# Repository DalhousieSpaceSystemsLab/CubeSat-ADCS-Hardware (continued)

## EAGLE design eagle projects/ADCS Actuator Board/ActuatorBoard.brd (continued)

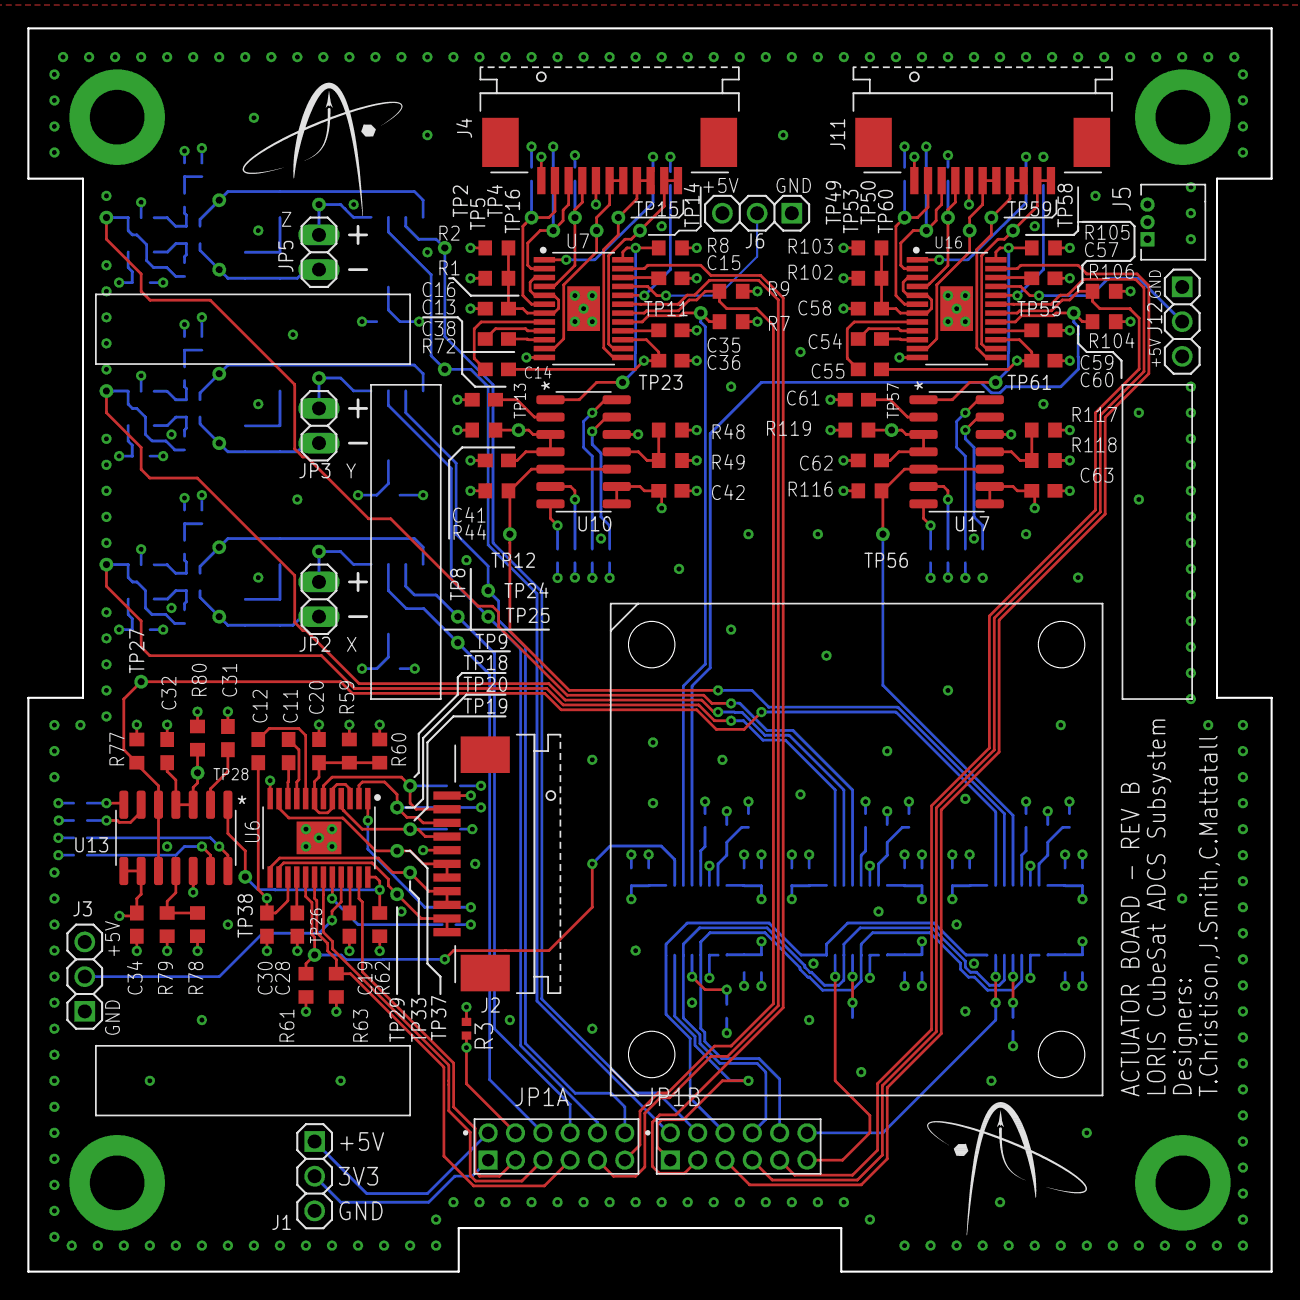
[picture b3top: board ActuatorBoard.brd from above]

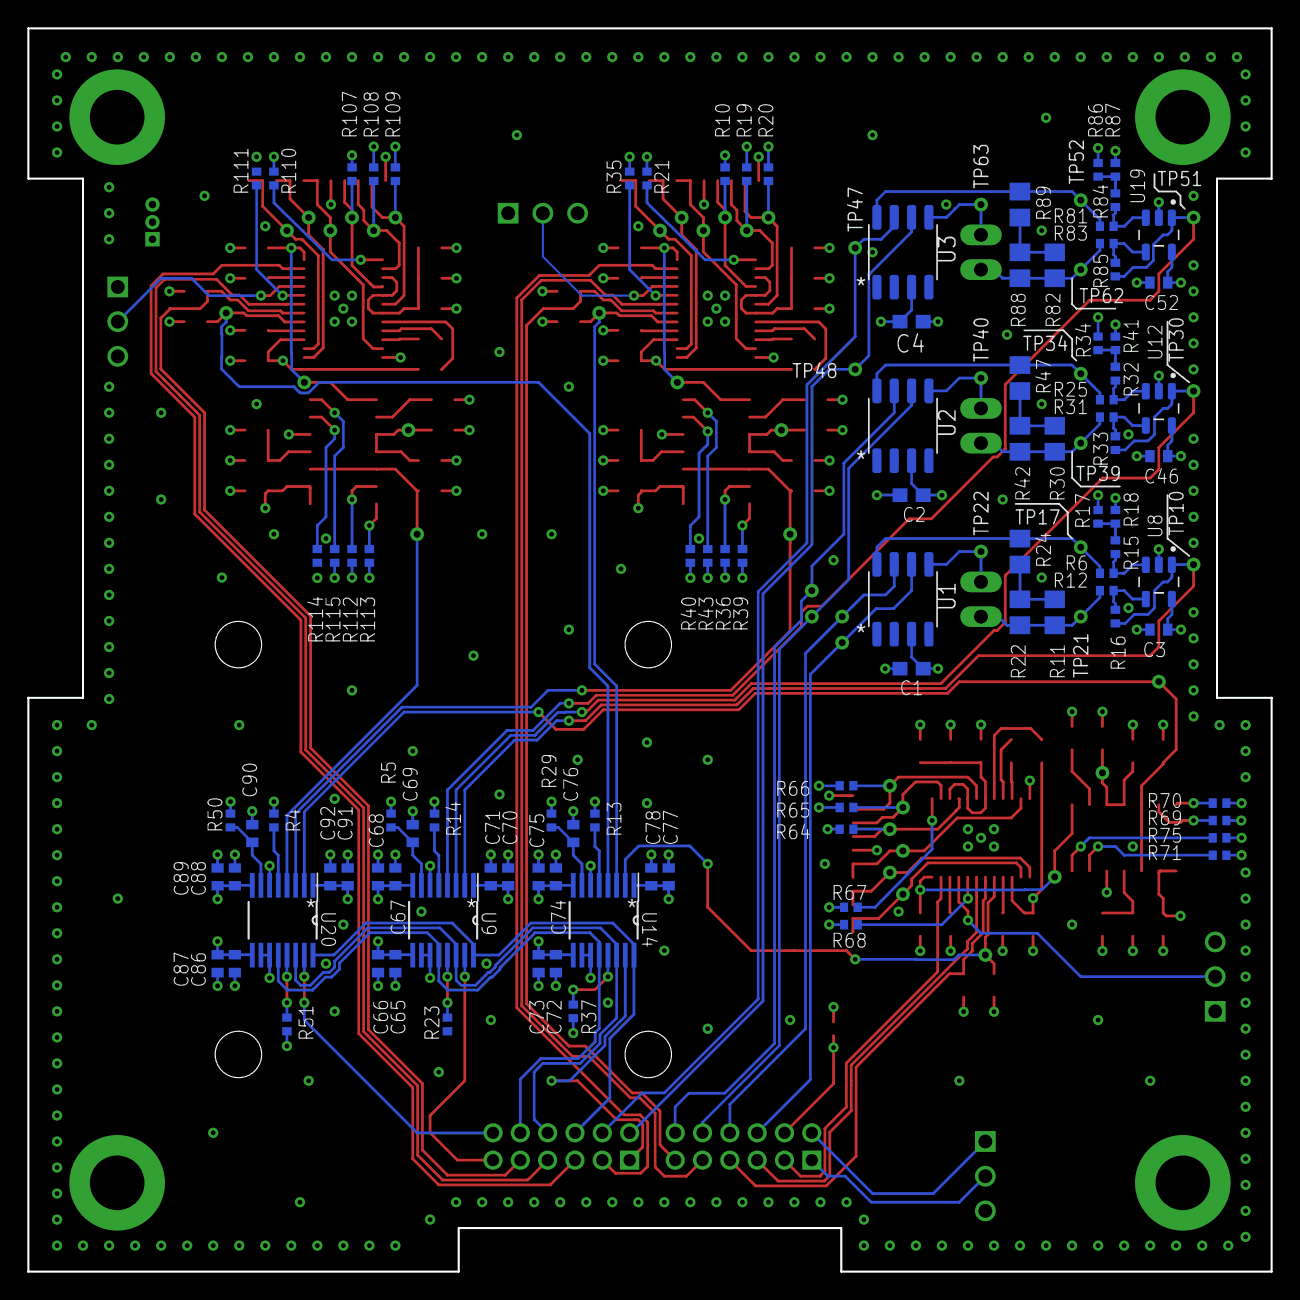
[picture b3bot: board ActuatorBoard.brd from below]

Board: 4 copper layers, 91.0 x 91.0 mm, 228 parts (117 on the bottom side), 133 nets.

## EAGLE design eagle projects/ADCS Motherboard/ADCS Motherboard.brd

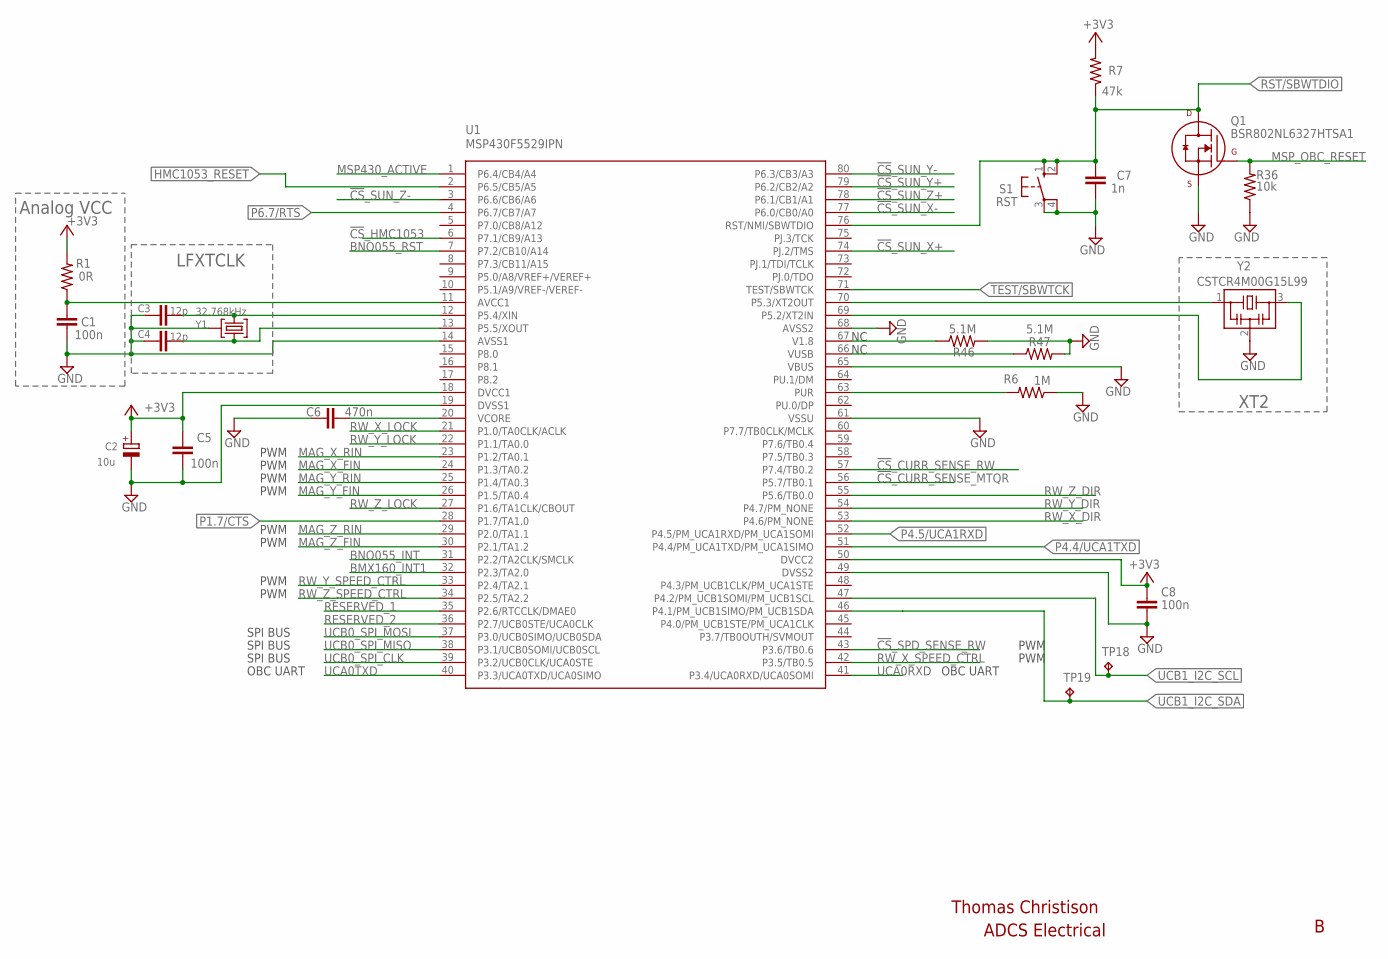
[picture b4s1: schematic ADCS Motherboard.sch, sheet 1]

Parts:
C1, C5, C8: 100n; C0402
C2: 10u; A/3216-18R
C3, C4: 12p; C0402
C6: 470n; C0402
C7: 1n; C0402
Q1: BSR802NL6327HTSA1; SOT23-3P95_230X110L20X43N_PMV16XN
R1: 0R; R0402
R6: 1M; R0603
R7: 47k; R0402
R36: 10k; R0603
R46, R47: 5.1M; R0402
S1: RST; B3F-10XX
TP18, TP19: TESTPOINT; TP_P76H50
U1: MSP430F5529IPN; QFP80P50_1400X1400X160L60X22N
Y1: 32.768kHz; MS3V-T1R
Y2: CSTCR4M00G15L99; MURATA-FILTER_CSTCR

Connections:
!CS!_CURR_SENSE_MTQR: U1.56 (P5.7/TB0.1); also elsewhere on the board
!CS!_CURR_SENSE_RW: U1.57 (P7.4/TB0.2); also elsewhere on the board
!CS!_HMC1053: U1.6 (P7.1/CB9/A13); also elsewhere on the board
!CS!_SPD_SENSE_RW: U1.43 (P3.6/TB0.6); also elsewhere on the board
!CS!_SUN_X+: U1.74 (PJ.2/TMS); also elsewhere on the board
!CS!_SUN_X-: U1.77 (P6.0/CB0/A0); also elsewhere on the board
!CS!_SUN_Y+: U1.79 (P6.2/CB2/A2); also elsewhere on the board
!CS!_SUN_Y-: U1.80 (P6.3/CB3/A3); also elsewhere on the board
!CS!_SUN_Z+: U1.78 (P6.1/CB1/A1); also elsewhere on the board
!CS!_SUN_Z-: U1.3 (P6.6/CB6/A6); also elsewhere on the board
+3V3: C2.+, C5.2, C8.1, R1.2, R7.2, U1.18 (DVCC1), U1.50 (DVCC2); also elsewhere on the board
AVCC1: C1.1, R1.1, U1.11 (AVCC1)
BMX160_INT1: U1.32 (P2.3/TA2.0); also elsewhere on the board
BNO055_INT: U1.31 (P2.2/TA2CLK/SMCLK); also elsewhere on the board
BNO055_RST: U1.7 (P7.2/CB10/A14); also elsewhere on the board
GND: C1.2, C2.-, C3.1, C4.1, C5.1, C6.1, C7.2, C8.2, Q1.2 (S), R6.1, R36.1, R46.2, R47.2, S1.3, S1.4 (P1), U1.14 (AVSS1), U1.19 (DVSS1), U1.49 (DVSS2), U1.61 (VSSU), U1.65 (VBUS), U1.68 (AVSS2), Y1.P3 (GND), Y2.2; also elsewhere on the board
HMC1053_RESET: U1.2 (P6.5/CB5/A5); also elsewhere on the board
MAG_X_FIN: U1.24 (P1.3/TA0.2); also elsewhere on the board
MAG_X_RIN: U1.23 (P1.2/TA0.1); also elsewhere on the board
MAG_Y_FIN: U1.26 (P1.5/TA0.4); also elsewhere on the board
MAG_Y_RIN: U1.25 (P1.4/TA0.3); also elsewhere on the board
MAG_Z_FIN: U1.30 (P2.1/TA1.2); also elsewhere on the board
MAG_Z_RIN: U1.29 (P2.0/TA1.1); also elsewhere on the board
MSP430_ACTIVE: U1.1 (P6.4/CB4/A4)
MSP_OBC_RESET: Q1.1 (G), R36.2; also elsewhere on the board
unnamed: R46.1, U1.67 (V1.8)
unnamed: R47.1, U1.66 (VUSB)
P1.7/CTS: U1.28 (P1.7/TA1.0); also elsewhere on the board
P4.4/UCA1TXD: U1.51 (P4.4/PM_UCA1TXD/PM_UCA1SIMO); also elsewhere on the board
P4.5/UCA1RXD: U1.52 (P4.5/PM_UCA1RXD/PM_UCA1SOMI); also elsewhere on the board
P5.2/XT2IN1: U1.69 (P5.2/XT2IN), Y2.3
P5.3/XT2OUT1: U1.70 (P5.3/XT2OUT), Y2.1
P5.4/XIN1: C3.2, U1.12 (P5.4/XIN), Y1.P2 (2)
P5.5/XOUT1: C4.2, U1.13 (P5.5/XOUT), Y1.P1 (1)
P6.7/RTS: U1.4 (P6.7/CB7/A7); also elsewhere on the board
RESERVED_1: U1.35 (P2.6/RTCCLK/DMAE0); also elsewhere on the board
RESERVED_2: U1.36 (P2.7/UCB0STE/UCA0CLK); also elsewhere on the board
RST/SBWTDIO: C7.1, Q1.3 (D), R7.1, S1.1 (S), S1.2 (S1), U1.76 (RST/NMI/SBWTDIO); also elsewhere on the board
RW_X_DIR: U1.53 (P4.6/PM_NONE); also elsewhere on the board
RW_X_LOCK: U1.21 (P1.0/TA0CLK/ACLK); also elsewhere on the board
RW_X_SPEED_CTRL: U1.42 (P3.5/TB0.5); also elsewhere on the board
RW_Y_DIR: U1.54 (P4.7/PM_NONE); also elsewhere on the board
RW_Y_LOCK: U1.22 (P1.1/TA0.0); also elsewhere on the board
RW_Y_SPEED_CTRL: U1.33 (P2.4/TA2.1); also elsewhere on the board
RW_Z_DIR: U1.55 (P5.6/TB0.0); also elsewhere on the board
RW_Z_LOCK: U1.27 (P1.6/TA1CLK/CBOUT); also elsewhere on the board
RW_Z_SPEED_CTRL: U1.34 (P2.5/TA2.2); also elsewhere on the board
TARGET_PUR: R6.2, U1.63 (PUR)
TEST/SBWTCK: U1.71 (TEST/SBWTCK); also elsewhere on the board
UCA0RXD: U1.41 (P3.4/UCA0RXD/UCA0SOMI); also elsewhere on the board
UCA0TXD: U1.40 (P3.3/UCA0TXD/UCA0SIMO); also elsewhere on the board
UCB0_SPI_CLK: U1.39 (P3.2/UCB0CLK/UCA0STE); also elsewhere on the board
UCB0_SPI_MISO: U1.38 (P3.1/UCB0SOMI/UCB0SCL); also elsewhere on the board
UCB0_SPI_MOSI: U1.37 (P3.0/UCB0SIMO/UCB0SDA); also elsewhere on the board
UCB1_I2C_SCL: TP18.1, U1.47 (P4.2/PM_UCB1SOMI/PM_UCB1SCL); also elsewhere on the board
UCB1_I2C_SDA: TP19.1, U1.46 (P4.1/PM_UCB1SIMO/PM_UCB1SDA); also elsewhere on the board
VCORE1: C6.2, U1.20 (VCORE)

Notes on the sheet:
LFXTCLK
XT2
Analog VCC
PWM
OBC UART
SPI BUS
Thomas Christison
ADCS Electrical

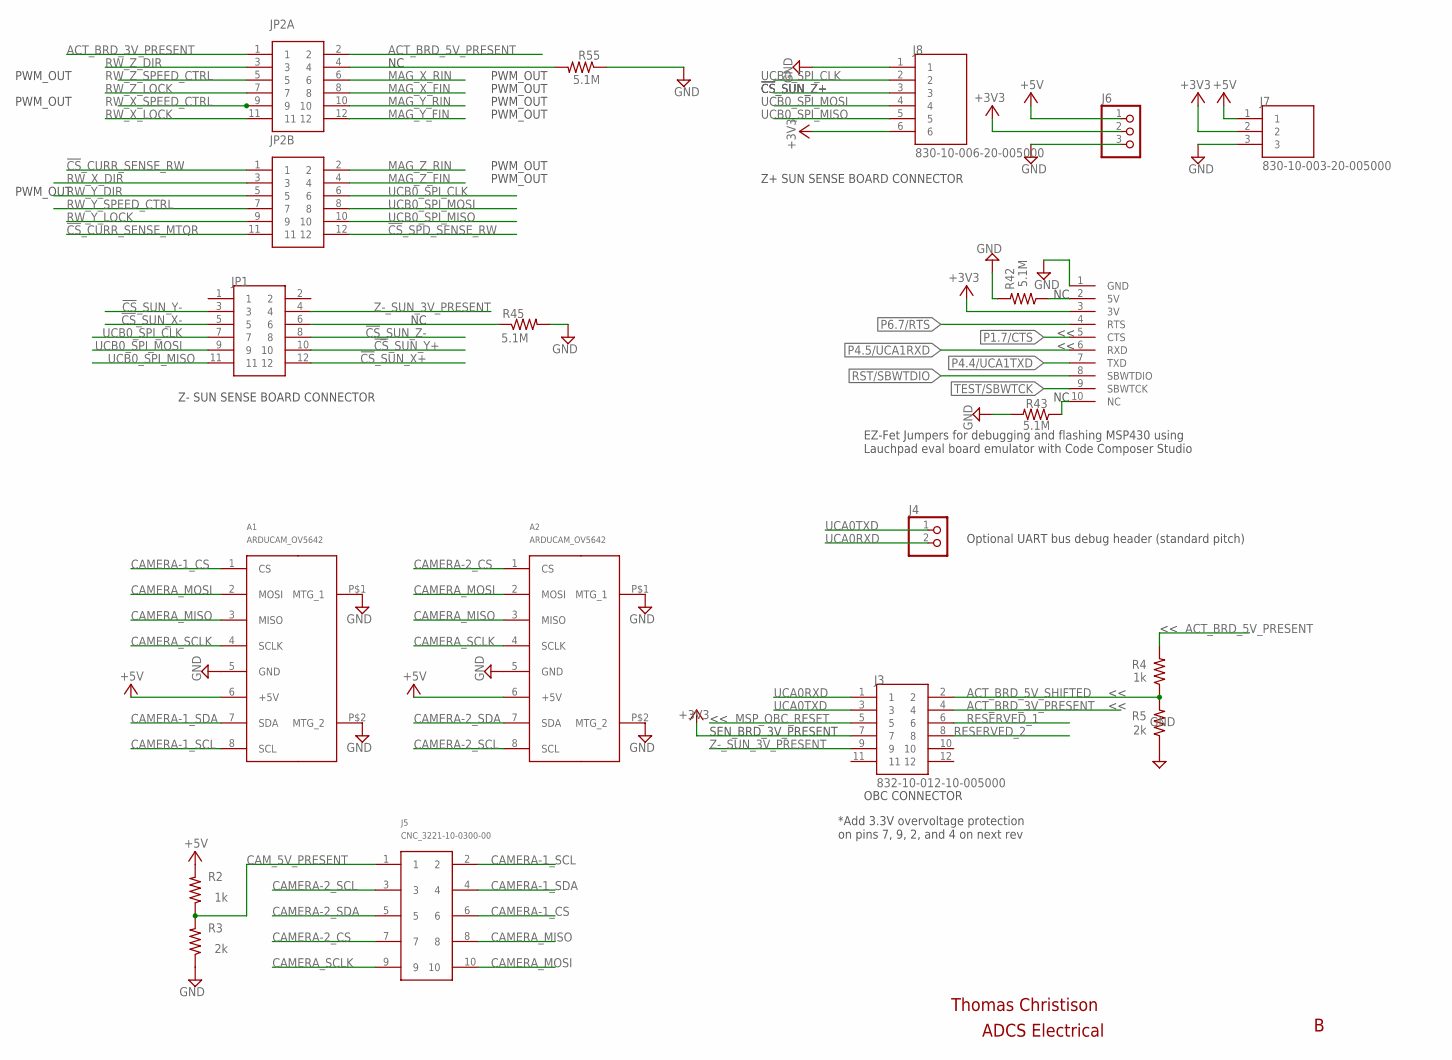
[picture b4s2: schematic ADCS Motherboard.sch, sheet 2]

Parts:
A1, A2: ARDUCAM_OV5642; ARDUCAM
J1: HDR_10_EZFET_DEBUGGER; HDRV10W66P254_10X1_2540X254H858
J3: 832-10-012-10-005000
J4: HDR_1X2_; 1X02
J5: CNC_3221-10-0300-00
J6: PINHD-1X3; 1X03
J7: 830-10-003-20-005000
J8: 830-10-006-20-005000
JP1, JP2A, JP2B: 832-10-012-10-005000
R2, R4: 1k; R0603
R3, R5: 2k; R0603
R42, R43, R45, R55: 5.1M; R0402

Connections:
!CS!_CURR_SENSE_MTQR: JP2B.11; also elsewhere on the board
!CS!_CURR_SENSE_RW: JP2B.1; also elsewhere on the board
!CS!_SPD_SENSE_RW: JP2B.12; also elsewhere on the board
!CS!_SUN_X+: JP1.12; also elsewhere on the board
!CS!_SUN_X-: JP1.5; also elsewhere on the board
!CS!_SUN_Y+: JP1.10; also elsewhere on the board
!CS!_SUN_Y-: JP1.3; also elsewhere on the board
!CS!_SUN_Z+: J8.3; also elsewhere on the board
!CS!_SUN_Z-: JP1.8; also elsewhere on the board
+3V3: J1.3 (3V), J3.7, J6.2, J7.2, J8.6; also elsewhere on the board
+5V: A1.6 (+5V), A2.6 (+5V), J6.1, J7.1, R2.2
ACT_BRD_3V_PRESENT: J3.4, JP2A.1
ACT_BRD_5V_PRESENT: JP2A.2, R4.2
ACT_BRD_5V_SHIFTED: J3.2, R4.1, R5.2
CAMERA-1_CS: A1.1 (CS), J5.6
CAMERA-1_SCL: A1.8 (SCL), J5.2
CAMERA-1_SDA: A1.7 (SDA), J5.4
CAMERA-2_CS: A2.1 (CS), J5.7
CAMERA-2_SCL: A2.8 (SCL), J5.3
CAMERA-2_SDA: A2.7 (SDA), J5.5
CAMERA_MISO: A1.3 (MISO), A2.3 (MISO), J5.8
CAMERA_MOSI: A1.2 (MOSI), A2.2 (MOSI), J5.10
CAMERA_SCLK: A1.4 (SCLK), A2.4 (SCLK), J5.9
CAM_5V_PRESENT: J5.1, R2.1, R3.2
GND: A1.5 (GND), A1.P$1 (MTG_1), A1.P$2 (MTG_2), A2.5 (GND), A2.P$1 (MTG_1), A2.P$2 (MTG_2), J1.1 (GND), J6.3, J7.3, J8.1, R3.1, R5.1, R42.2, R43.2, R45.2, R55.1; also elsewhere on the board
MAG_X_FIN: JP2A.8; also elsewhere on the board
MAG_X_RIN: JP2A.6; also elsewhere on the board
MAG_Y_FIN: JP2A.12; also elsewhere on the board
MAG_Y_RIN: JP2A.10; also elsewhere on the board
MAG_Z_FIN: JP2B.4; also elsewhere on the board
MAG_Z_RIN: JP2B.2; also elsewhere on the board
MSP_OBC_RESET: J3.5; also elsewhere on the board
unnamed: JP2A.4, R55.2
unnamed: J1.2 (5V), R42.1
unnamed: J1.10 (NC), R43.1
unnamed: JP1.6, R45.1
P1.7/CTS: J1.5 (CTS); also elsewhere on the board
P4.4/UCA1TXD: J1.7 (TXD); also elsewhere on the board
P4.5/UCA1RXD: J1.6 (RXD); also elsewhere on the board
P6.7/RTS: J1.4 (RTS); also elsewhere on the board
RESERVED_1: J3.6; also elsewhere on the board
RESERVED_2: J3.8; also elsewhere on the board
RST/SBWTDIO: J1.8 (SBWTDIO); also elsewhere on the board
RW_X_DIR: JP2B.3; also elsewhere on the board
RW_X_LOCK: JP2A.11; also elsewhere on the board
RW_X_SPEED_CTRL: JP2A.9; also elsewhere on the board
RW_Y_DIR: JP2B.5; also elsewhere on the board
RW_Y_LOCK: JP2B.9; also elsewhere on the board
RW_Y_SPEED_CTRL: JP2B.7; also elsewhere on the board
RW_Z_DIR: JP2A.3; also elsewhere on the board
RW_Z_LOCK: JP2A.7; also elsewhere on the board
RW_Z_SPEED_CTRL: JP2A.5; also elsewhere on the board
TEST/SBWTCK: J1.9 (SBWTCK); also elsewhere on the board
UCA0RXD: J3.1, J4.2; also elsewhere on the board
UCA0TXD: J3.3, J4.1; also elsewhere on the board
UCB0_SPI_CLK: J8.2, JP1.7, JP2B.6; also elsewhere on the board
UCB0_SPI_MISO: J8.5, JP1.11, JP2B.10; also elsewhere on the board
UCB0_SPI_MOSI: J8.4, JP1.9, JP2B.8; also elsewhere on the board
Z-_SUN_3V_PRESENT: J3.9, JP1.4

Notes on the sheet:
PWM_OUT
OBC CONNECTOR
SEN_BRD_3V_PRESENT
*Add 3.3V overvoltage protection on pins 7, 9, 2, and 4 on next rev
EZ-Fet Jumpers for debugging and flashing MSP430 using Lauchpad eval board emulator with Code Composer Studio
Optional UART bus debug header (standard pitch)
Z- SUN SENSE BOARD CONNECTOR
Z+ SUN SENSE BOARD CONNECTOR
Thomas Christison
ADCS Electrical

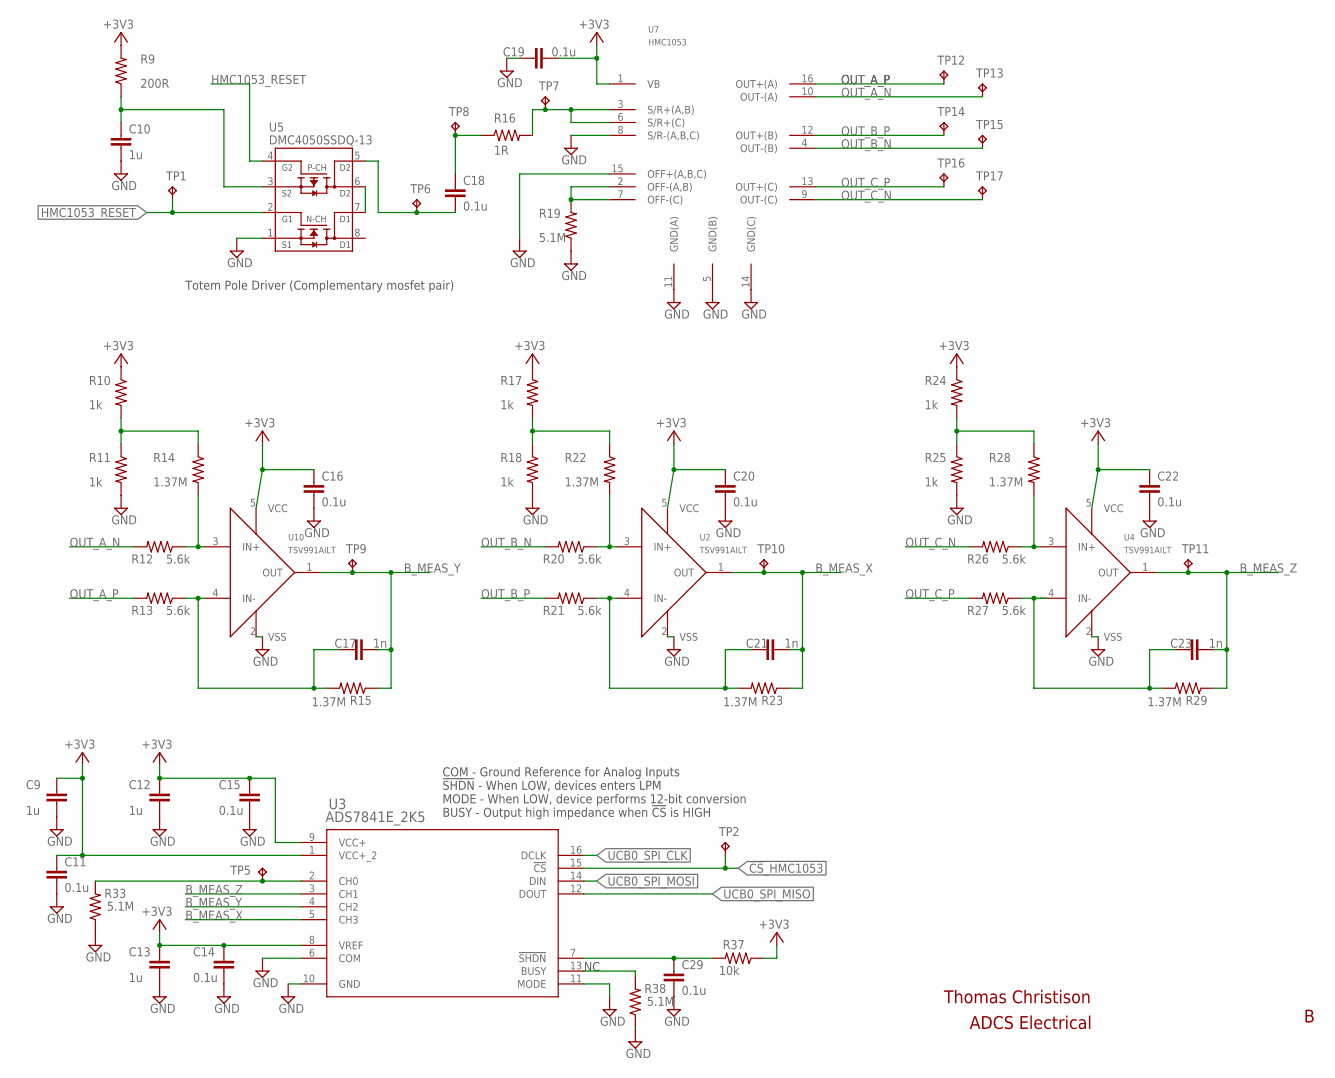
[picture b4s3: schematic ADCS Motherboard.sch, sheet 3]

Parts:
C9, C12, C13: 1u; C0805
C10: 1u; C0603
C11, C14, C15, C16, C19, C20, C22, C29: 0.1u; C0603
C17, C21, C23: 1n; C0603
C18: 0.1u; C0805
R9: 200R; R0805
R10, R11, R17, R18, R24, R25: 1k; R0603
R12, R13, R20, R21, R26, R27: 5.6k; R0603
R14, R15, R22, R23, R28, R29: 1.37M; R0603
R16: 1R; R0805
R19, R33, R38: 5.1M; R0402
R37: 10k; R0603
TP1, TP2, TP5, TP6, TP7, TP8, TP9, TP10, TP11, TP12, TP13, TP14, TP15, TP16, TP17: TESTPOINT; TP_P76H50
U2, U4, U10: TSV991AILT; SOT95P280X145-5N
U3: ADS7841E_2K5; DBQ16
U5: DMC4050SSDQ-13; SOIC8P127_490X600X175L72X40N_DMC4050SSDQ-13
U7: HMC1053; LCCS16P127_736X736X279L127X50N

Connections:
!CS!_HMC1053: TP2.1, U3.15 (!CS); also elsewhere on the board
+3V3: C9.1, C11.1, C12.1, C13.1, C14.1, C15.1, C16.1, C19.1, C20.1, C22.1, R9.2, R10.1, R17.1, R24.1, R37.1, U2.5 (VCC), U3.1 (VCC+_2), U3.8 (VREF), U3.9 (VCC+), U4.5 (VCC), U7.1 (VB), U10.5 (VCC); also elsewhere on the board
B_MEAS_X: C21.2, R23.1, TP10.1, U2.1 (OUT), U3.5 (CH3)
B_MEAS_Y: C17.2, R15.1, TP9.1, U3.4 (CH2), U10.1 (OUT)
B_MEAS_Z: C23.2, R29.1, TP11.1, U3.3 (CH1), U4.1 (OUT)
GND: C9.2, C10.1, C11.2, C12.2, C13.2, C14.2, C15.2, C16.2, C19.2, C20.2, C22.2, C29.2, R11.2, R18.2, R19.1, R25.2, R33.1, R38.1, U2.2 (VSS), U3.6 (COM), U3.10 (GND), U3.11 (MODE), U4.2 (VSS), U5.1 (S1), U7.5 (GND(B)), U7.8 (S/R-(A,B,C)), U7.11 (GND(A)), U7.14 (GND(C)), U7.15 (OFF+(A,B,C)), U10.2 (VSS); also elsewhere on the board
HMC1053_RESET: TP1.1, U5.2 (G1), U5.4 (G2); also elsewhere on the board
unnamed: C18.1, TP6.1, U5.5 (D2_2)
unnamed: R10.2, R11.1, R14.1
unnamed: C17.1, R13.1, R15.2, U10.4 (IN-)
unnamed: R12.1, R14.2, U10.3 (IN+)
unnamed: R33.2, TP5.1, U3.2 (CH0)
unnamed: R38.2, U3.13 (BUSY)
unnamed: C29.1, R37.2, U3.7 (!SHDN)
unnamed: C18.2, R16.1, TP8.1
unnamed: R19.2, U7.2 (OFF-(A,B)), U7.7 (OFF-(C))
unnamed: R16.2, TP7.1, U7.3 (S/R+(A,B)), U7.6 (S/R+(C))
unnamed: C10.2, R9.1, U5.3 (S2)
unnamed: U5.6 (D2_1), U5.7 (D1_2)
unnamed: R17.2, R18.1, R22.1
unnamed: C21.1, R21.1, R23.2, U2.4 (IN-)
unnamed: R20.1, R22.2, U2.3 (IN+)
unnamed: R24.2, R25.1, R28.1
unnamed: C23.1, R27.1, R29.2, U4.4 (IN-)
unnamed: R26.1, R28.2, U4.3 (IN+)
OUT_A_N: R12.2, TP13.1, U7.10 (OUT-(A))
OUT_A_P: R13.2, TP12.1, U7.16 (OUT+(A))
OUT_B_N: R20.2, TP15.1, U7.4 (OUT-(B))
OUT_B_P: R21.2, TP14.1, U7.12 (OUT+(B))
OUT_C_N: R26.2, TP17.1, U7.9 (OUT-(C))
OUT_C_P: R27.2, TP16.1, U7.13 (OUT+(C))
UCB0_SPI_CLK: U3.16 (DCLK); also elsewhere on the board
UCB0_SPI_MISO: U3.12 (DOUT); also elsewhere on the board
UCB0_SPI_MOSI: U3.14 (DIN); also elsewhere on the board

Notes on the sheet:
COM - Ground Reference for Analog Inputs !SHDN! - When LOW, devices enters LPM MODE - When LOW, device performs 12-bit conversion BUSY - Output high impedance when !CS! is HIGH
Totem Pole Driver (Complementary mosfet pair)
Thomas Christison
ADCS Electrical

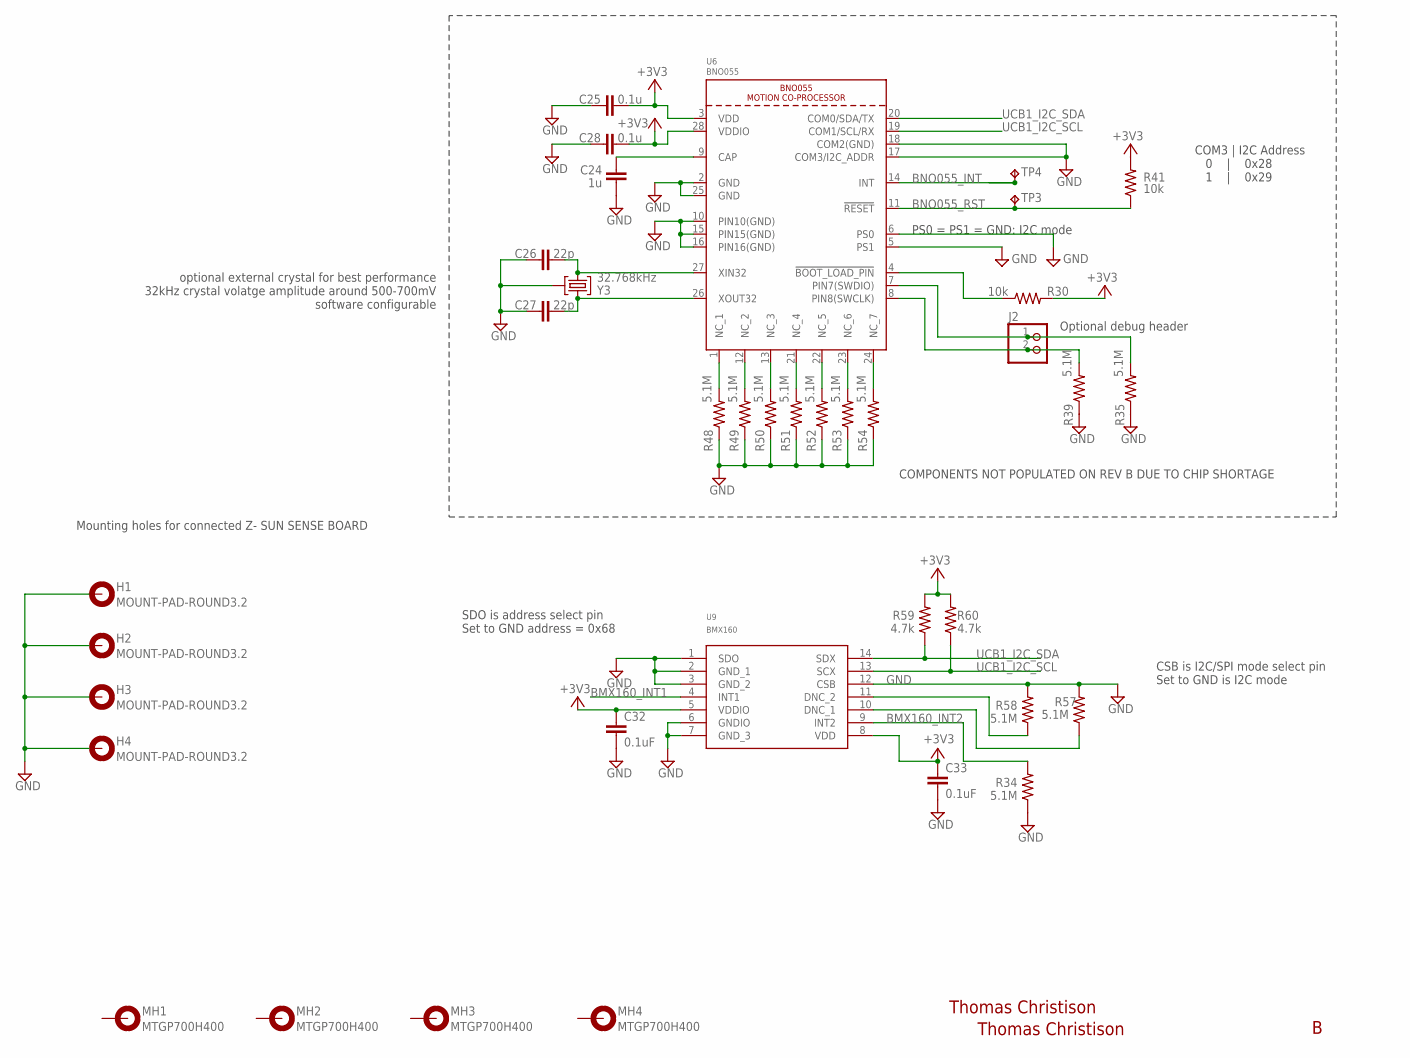
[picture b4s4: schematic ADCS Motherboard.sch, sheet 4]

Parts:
C24: 1u; C0402
C25, C28: 0.1u; C0402
C26, C27: 22p; C0402
C32, C33: 0.1uF; C0805
H1, H2, H3, H4: MOUNT-PAD-ROUND3.2; 3,2-PAD
J2: HDR_1X2_; 1X02
MH1, MH2, MH3, MH4: MTGP700H400
R30, R41: 10k; R0402
R34, R35, R39, R48, R49, R50, R51, R52, R53, R54, R57, R58: 5.1M; R0402
R59, R60: 4.7k; R0603
TP3, TP4: TESTPOINT; TP_P76H50
U6: BNO055
U9: BMX160; QFN14P50_300X250X100L47X25N
Y3: 32.768kHz; MS3V-T1R

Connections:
+3V3: C25.2, C28.2, C32.1, C33.1, R30.2, R41.2, R59.2, R60.2, U6.3 (VDD), U6.28 (VDDIO), U9.5 (VDDIO), U9.8 (VDD); also elsewhere on the board
BMX160_INT1: U9.4 (INT1); also elsewhere on the board
BMX160_INT2: R34.2, U9.9 (INT2)
BNO055_INT: TP4.1, U6.14 (INT); also elsewhere on the board
BNO055_RST: R41.1, TP3.1, U6.11 (!RESET); also elsewhere on the board
GND: C24.1, C25.1, C26.1, C27.1, C28.1, C32.2, C33.2, H1.B3,2, H2.B3,2, H3.B3,2, H4.B3,2, R34.1, R35.1, R39.1, R48.1, R49.1, R50.1, R51.1, R52.1, R53.1, R54.1, R57.2, R58.2, U6.2 (GND), U6.5 (PS1), U6.6 (PS0), U6.10 (PIN10(GND)), U6.15 (PIN15(GND)), U6.16 (PIN16(GND)), U6.17 (COM3/I2C_ADDR), U6.18 (COM2(GND)), U6.25 (GND), U9.1 (SDO), U9.2 (GND_1), U9.3 (GND_2), U9.6 (GNDIO), U9.7 (GND_3), U9.12 (CSB), Y3.P3 (GND); also elsewhere on the board
unnamed: R30.1, U6.4 (!BOOT_LOAD_PIN)
unnamed: C24.2, U6.9 (CAP)
unnamed: C26.2, U6.27 (XIN32), Y3.P1 (1)
unnamed: C27.2, U6.26 (XOUT32), Y3.P2 (2)
unnamed: J2.1, R35.2, U6.7 (PIN7(SWDIO))
unnamed: J2.2, R39.2, U6.8 (PIN8(SWCLK))
unnamed: R58.1, U9.11 (DNC_2)
unnamed: R57.1, U9.10 (DNC_1)
unnamed: R48.2, U6.1 (NC_1)
unnamed: R49.2, U6.12 (NC_2)
unnamed: R50.2, U6.13 (NC_3)
unnamed: R51.2, U6.21 (NC_4)
unnamed: R52.2, U6.22 (NC_5)
unnamed: R53.2, U6.23 (NC_6)
unnamed: R54.2, U6.24 (NC_7)
UCB1_I2C_SCL: R60.1, U6.19 (COM1/SCL/RX), U9.13 (SCX); also elsewhere on the board
UCB1_I2C_SDA: R59.1, U6.20 (COM0/SDA/TX), U9.14 (SDX); also elsewhere on the board

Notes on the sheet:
optional external crystal for best performance 32kHz crystal volatge amplitude around 500-700mV software configurable
Optional debug header
PS0 = PS1 = GND: I2C mode
COM3 | I2C Address 0 | 0x28 1 | 0x29
Mounting holes for connected Z- SUN SENSE BOARD
COMPONENTS NOT POPULATED ON REV B DUE TO CHIP SHORTAGE
SDO is address select pin Set to GND address = 0x68
CSB is I2C/SPI mode select pin Set to GND is I2C mode
Thomas Christison

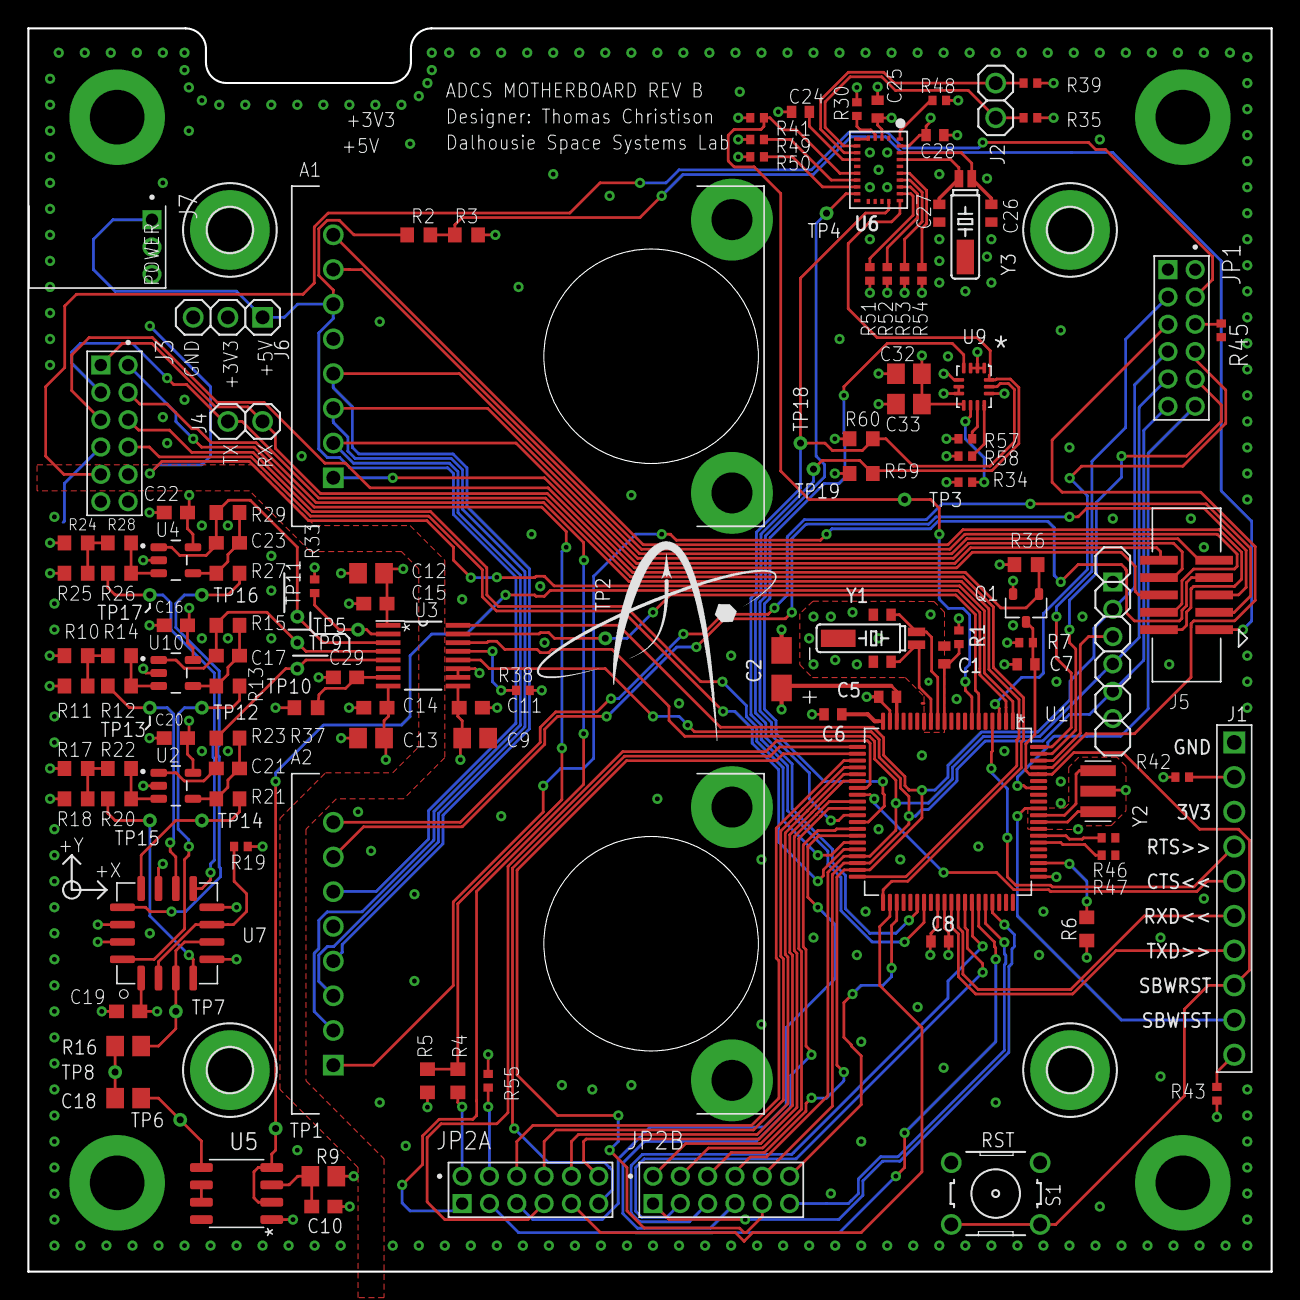
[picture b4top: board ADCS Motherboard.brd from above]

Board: 4 copper layers, 91.0 x 91.0 mm, 139 parts (1 on the bottom side), 118 nets.

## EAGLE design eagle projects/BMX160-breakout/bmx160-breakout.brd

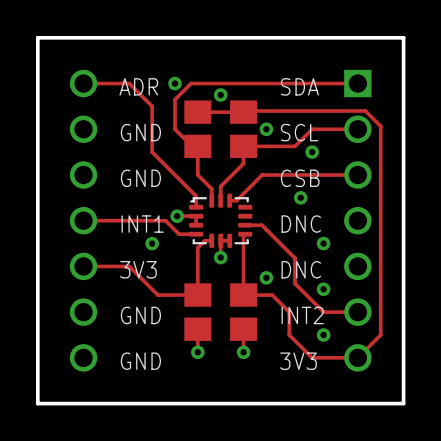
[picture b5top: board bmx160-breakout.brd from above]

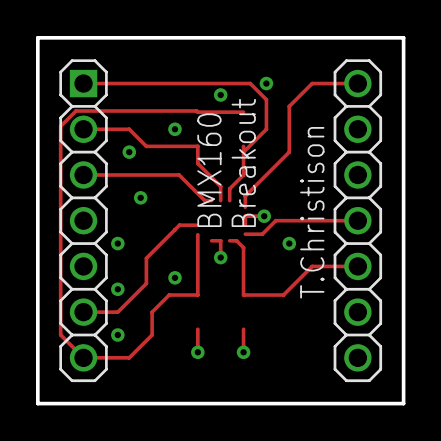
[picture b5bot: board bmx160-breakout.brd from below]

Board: 2 copper layers, 20.3 x 20.3 mm, 7 parts (2 on the bottom side), 8 nets.

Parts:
C1, C2: 0.1uF; C0805
JP1: 1X07
JP2: 1X07*
R1, R2: 4.7k; R0805
U1: BMX160; QFN14P50_300X250X100L47X25N

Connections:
+3V3: C1.1, C2.1, JP1.7, JP2.5, R1.2, R2.2, U1.5, U1.8
CSB: JP1.3, U1.12
GND: C1.2, C2.2, JP2.2, JP2.3, JP2.6, JP2.7, U1.2, U1.3, U1.6, U1.7
INT1: JP2.4, U1.4
INT2: JP1.6, U1.9
SCL: JP1.2, R2.1, U1.13
SDA: JP1.1, R1.1, U1.14
SDO: JP2.1, U1.1

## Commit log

2021-06-18 Added iMU breakout board for BMX160
2021-06-18 Staring REV B Act board
2021-06-21 Added FV converters, replaced connectors
2021-06-21 Replaced connectors for Rev B
2021-06-22 Ton of layout changes.. too many to count but this is rev b
2021-06-23 Possibly done rev b mobo??
2021-06-24 Added Actuator brd to mobo flex connector
2021-06-24 Added power connector and mobo-act brd mounting holes
2021-06-24 Added mobo-act brd mounting holes
2021-06-24 Added mounting holes for M2 screws
2021-06-28 Rev B almost ready
2021-07-13 Idk what i changed
2021-07-13 Replace totem pole driver with complementary Mosfets pair package
2021-07-13 Added new mosfet pair to layout
2021-07-14 Added cut to sun sense board for magnetorquer passthru
2021-07-14 Grounded standoff mounting hole pins
2021-07-20 Stitching vias, new current limit res for motors, updated motor retry cap
2021-07-21 Lengthened one of the flex connectors
2021-07-22 Replaced h-bridges with substitute part
2021-07-22 Moved text
2021-07-22 Created 5x2 SMD 2.54mm footprint and added it to board that needs it
2021-07-23 Silkscreen updates
2021-07-24 stitching vias and silkscreen and fixed reversed totem pole driver (oops)
2021-07-26 I thinks its done
2021-07-26 silk screen
2021-07-26 Brandon added burn resistor components
2021-07-26 Brandon changed the location of cutting resistor to top left
2021-07-26 finilized rev b layout
2021-07-26 done z plus
2021-07-27 done
2021-07-28 dumb dumb fix dumb mistake
2021-07-29 Added 24 pin SMD header and lengthened both connectors
2021-07-29 Added stiffener polygons
2021-07-29 Adding REV B pcb release files
2021-08-05 Mirrored one of the connectors ends (incorrectly)
2021-08-12 Fixed Connector Boards
2021-10-06 Updated XY Sun Sensor Board
2021-10-21 Added proper connectors on XY Sun Connectors
2021-10-23 Added Folder of New Solder Cup Connectors
2021-10-23 Solder Cups on Z+ Board
    Replace previous connector on Z+ Sun Sensor Board with solder cups. Rearranged wires to fit the new component.
2021-10-23 Changed most connector changes of Z- board
2021-10-23 Solder Cups on Motherboard
    Started swapping connectors on Motherboard
2021-11-05 Finished Z- Sun Sensor
2021-11-05 Cleaned up errors in Z+ and Z- boards
2021-11-05 Partially Replaced Connectors on Actuator
    Will finish soon
2021-11-05 Changed out OBC connector on motherboard
2021-11-05 Arranged 12x2 Connectors on Motherboard and Actuator Board
    Unfinished, needs cleanup
2021-11-06 Finished updating connectors of mother board
2021-11-06 Finished all new connectors
2021-11-06 Final update to PCB connectors
2021-11-09 Centered connector on Actuator Board
2021-11-10 Added BOMs
2021-11-11 Updated footprint names
2021-11-11 Removed LED to Z-
    Removed a voltage testing LED and associated resistor from the Z- board, BOM was updated accordingly.
2021-11-11 Removed LEDs from MOBO
2021-11-11 Removed LEDs from actuator board
    Removed power reader LEDs from actuator boards. Associated resistors were also removed and BOM was updated.
2021-11-11 Air wires and wire stubs fixed on all boards
2021-11-11 Added new BOMs
2021-11-17 Added Luc's recommended new power connectors
2021-11-17 Changed camera hole sizes on Z+
2021-11-17 Updated Actuator board BOM and populated necessary resistors on Z+ board
2021-11-21 Revert "Added Luc's recommended new power connectors"
    This reverts commit dfe48c56fe37fa57a9af7eb032061edffce3900f.
2021-11-22 Finalized connectors for Luc and reattached burn wire
2021-11-24 Updated BOMs
2021-11-26 BOM Updates
    New BOM sheet for ICs, made some fixes to the Z+ BOM
2021-11-29 IC BOM Updates
2022-01-12 Added patch antennae on separate version of Z-
